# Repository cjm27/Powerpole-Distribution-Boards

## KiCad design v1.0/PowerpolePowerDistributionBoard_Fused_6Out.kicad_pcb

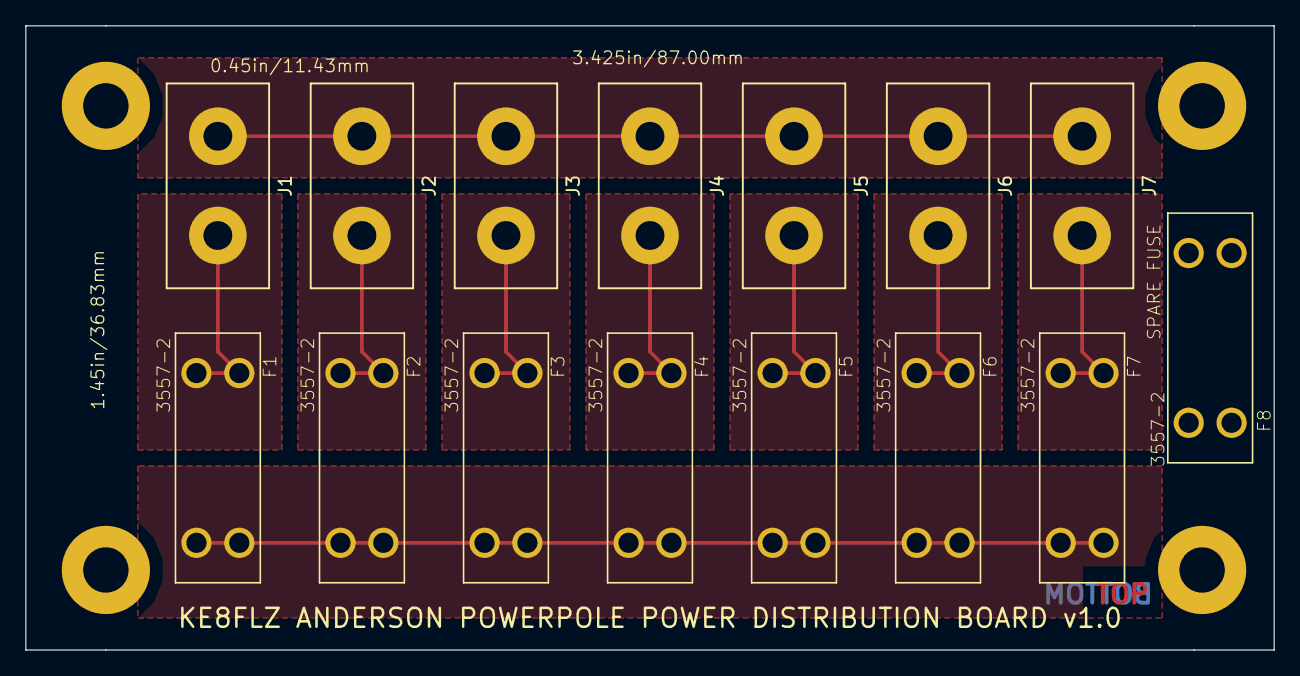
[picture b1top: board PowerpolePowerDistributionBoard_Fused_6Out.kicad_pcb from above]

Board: 2 copper layers, 99.1 x 49.5 mm, 15 parts (0 on the bottom side), 9 nets.

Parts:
3557-2: F8; FUSE_3557-2
F1, F2, F3, F4, F5, F6, F7: 3557-2; FUSE_3557-2
J1, J2, J3, J4, J5, J6, J7: AndersonPowerpole; Powerpole_PP15-45_12ga_Wire

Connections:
unnamed: F1.1, F1.2, J1.1
unnamed: F1.3, F1.4, F2.3, F2.4, F3.3, F3.4, F4.3, F4.4, F5.3, F5.4, F6.3, F6.4, F7.3, F7.4
unnamed: F2.1, F2.2, J2.1
unnamed: F3.1, F3.2, J3.1
unnamed: F4.1, F4.2, J4.1
unnamed: F5.1, F5.2, J5.1
unnamed: F6.1, F6.2, J6.1
unnamed: F7.1, F7.2, J7.1
unnamed: J1.2, J2.2, J3.2, J4.2, J5.2, J6.2, J7.2

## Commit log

2017-06-20 v0.1
